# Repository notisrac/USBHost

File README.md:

# USB host for Arduino

A PCB for HobbyTronics' USB host board:  [http://www.hobbytronics.co.uk/usb-host-board-v2](http://www.hobbytronics.co.uk/usb-host-board-v2)

*Please note, this design is based on an earlier version of the schematic, thus lacks a few features, like the reset button!*

## Pictures
Assembled:

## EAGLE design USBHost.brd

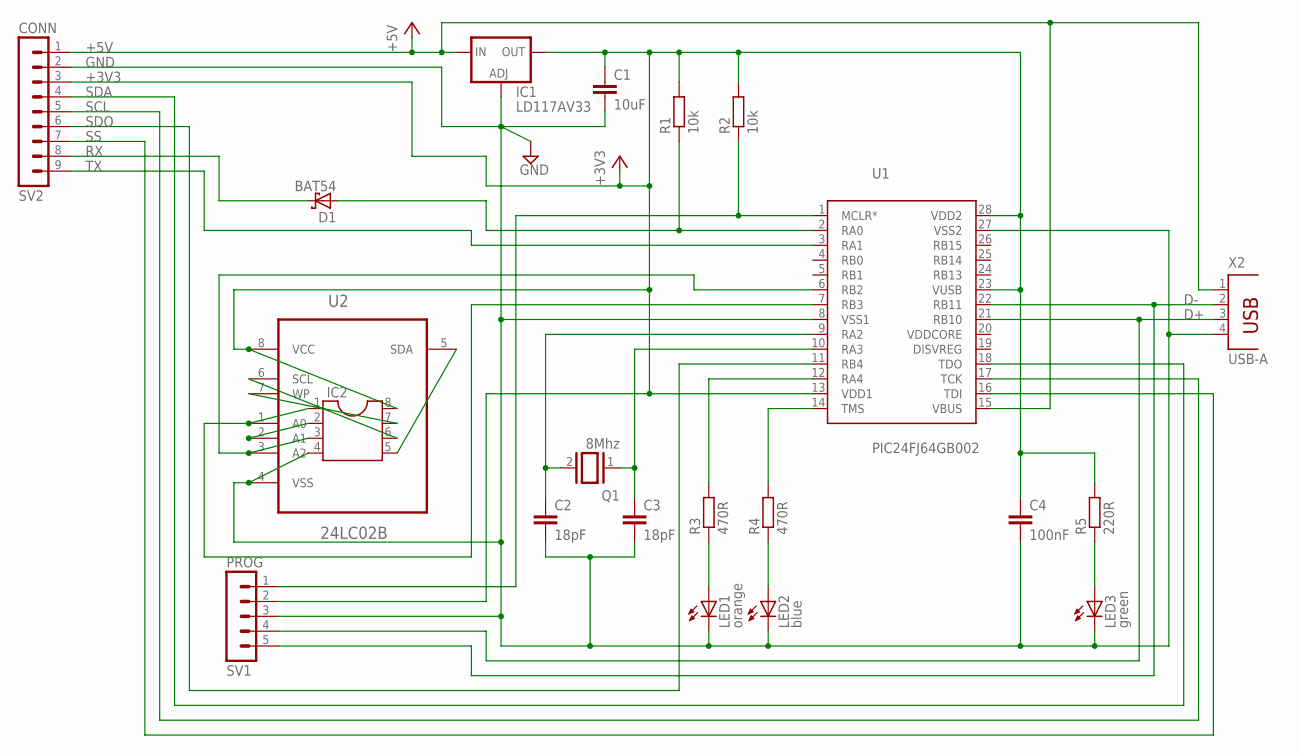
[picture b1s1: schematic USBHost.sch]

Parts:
C1: 10uF; C025-025X050
C2, C3: 18pF; C025-025X050
C4: 100nF; C025-025X050
D1: BAT54; DO35-7
IC1: LD117AV33; TO220L1
IC2: DIL8S; SOCKET-08
LED1: orange; LED5MM
LED2: blue; LED5MM
LED3: green; LED5MM
Q1: 8Mhz; QS
R1, R2: 10k; 0204/7
R3, R4: 470R; 0204/7
R5: 220R; 0204/7
SV1: PROG; MA05-1
SV2: CONN; MA09-1
U1: PIC24FJ64GB002; DIP254P762X508-28
U2: 24LC02B; SOIC127P600X175-8N
X2: USB-A; PN87520

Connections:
+3V3: C1.1, C4.1, IC1.2 (OUT), IC2.8, R1.2, R2.2, R5.2, SV1.2, SV2.3, U1.13 (VDD1), U1.23 (VUSB), U1.28 (VDD2), U2.8 (VCC)
+5V: IC1.3 (IN), SV2.1, U1.15 (VBUS), X2.1
D+: SV1.4, U1.21 (RB10), X2.3
D-: SV1.5, U1.22 (RB11), X2.2
GND: C1.2, C2.2, C3.2, C4.2, IC1.1 (ADJ), IC2.4, LED1.K (C), LED2.K (C), LED3.K (C), SV1.3, SV2.2, U1.8 (VSS1), U1.27 (VSS2), U2.4 (VSS), X2.4
unnamed: C3.1, Q1.1, U1.10 (RA3)
unnamed: C2.1, Q1.2, U1.9 (RA2)
unnamed: LED3.A, R5.1
unnamed: R2.1, SV1.1, U1.1 (MCLR*)
unnamed: LED2.A, R4.1
unnamed: LED1.A, R3.1
unnamed: R4.2, U1.14 (TMS)
unnamed: R3.2, U1.12 (RA4)
unnamed: D1.A, R1.1, U1.2 (RA0)
unnamed: IC2.2, U2.2 (A1)
unnamed: IC2.3, U1.6 (RB2), U2.3 (A2)
unnamed: IC2.1, U1.7 (RB3), U2.1 (A0)
unnamed: IC2.5, U2.5 (SDA)
unnamed: IC2.6, U2.6 (SCL)
unnamed: IC2.7, U2.7 (WP)
RX: D1.C, SV2.8
SCL: SV2.5, U1.17 (TCK)
SDA: SV2.4, U1.18 (TDO)
SDO: SV2.6, U1.11 (RB4)
SS: SV2.7, U1.16 (TDI)
TX: SV2.9, U1.3 (RA1)
VDDCORE: U1.20 (VDDCORE)

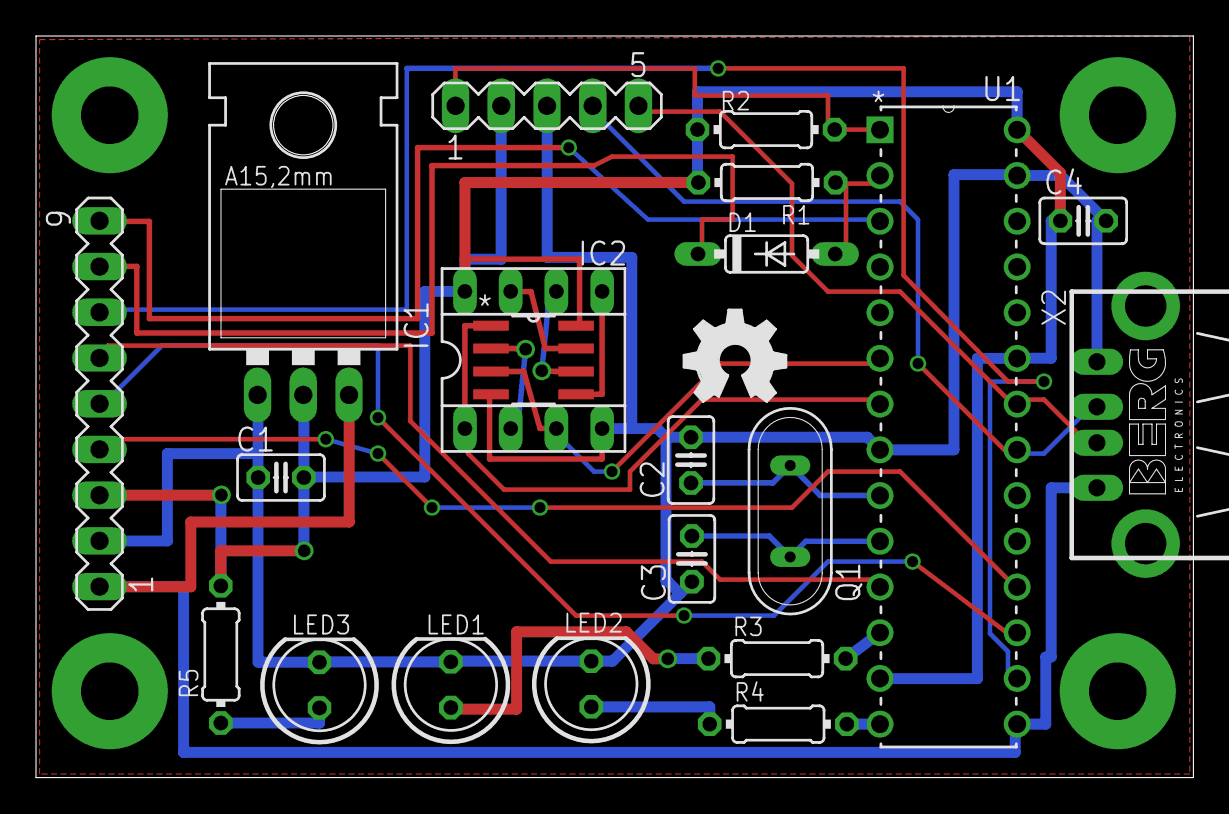
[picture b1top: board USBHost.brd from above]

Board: 2 copper layers, 64.3 x 41.2 mm, 22 parts (0 on the bottom side), 26 nets.

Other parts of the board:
U$1: OSHW_FILLX200_NOTEXT

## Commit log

2016-02-07 - Fixed: typo in README.md
2018-07-27 Fixed README issues
2018-07-28 Added GA beacon to the README
2018-07-29 Added gitattributes
2018-07-29 Removed epf file
